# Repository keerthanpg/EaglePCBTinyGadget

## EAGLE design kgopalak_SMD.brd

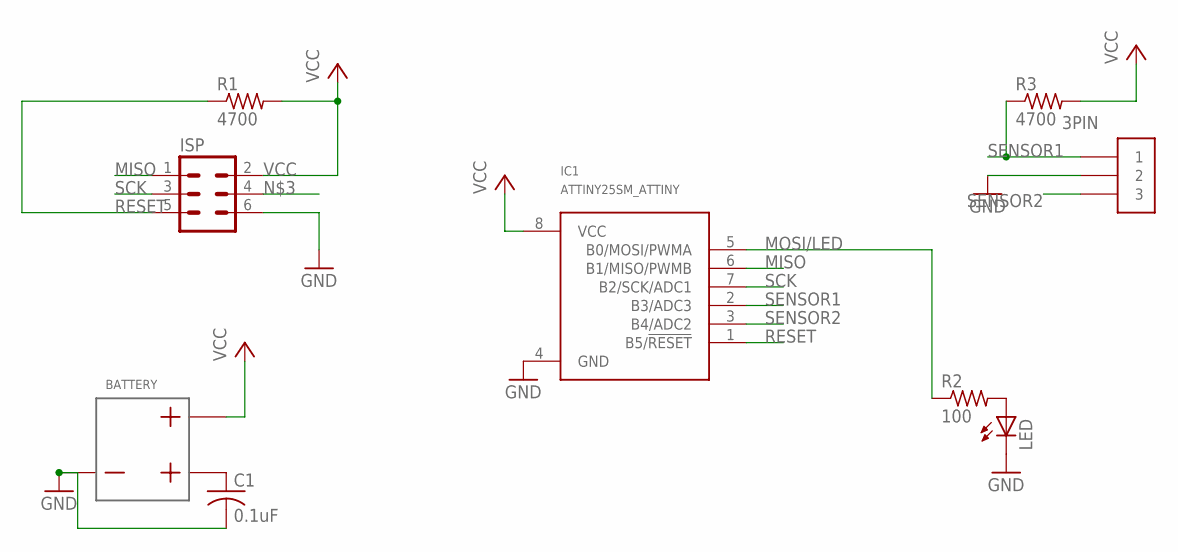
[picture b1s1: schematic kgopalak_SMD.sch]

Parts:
3PIN: 3PINCONSM_3PIN; SM3PIN
BATTERY: BATTERYSM_BA2032; BA2032SM
C1: 0.1uF; C0402
IC1: ATTINY25SM_ATTINY; 8S1
ISP: 6PINCON_ISPSM_6PIN; SM6PIN
LED: LEDSMLED; CHIPLED_0603
R1, R3: 4700; R0402
R2: 100; R0402

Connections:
GND: 3PIN.2, BATTERY.1, C1.2, IC1.4 (GND), ISP.6, LED.C
MISO: IC1.6 (B1/MISO/PWMB), ISP.1
MOSI/LED: IC1.5 (B0/MOSI/PWMA), R2.1
unnamed: LED.A, R2.2
unnamed: BATTERY.3, C1.1
RESET: IC1.1 (B5/!RESET), ISP.5, R1.1
SCK: IC1.7 (B2/SCK/ADC1), ISP.3
SENSOR1: 3PIN.1, IC1.2 (B3/ADC3), R3.1
SENSOR2: 3PIN.3, IC1.3 (B4/ADC2)
VCC: BATTERY.2, IC1.8 (VCC), ISP.2, R1.2, R3.2

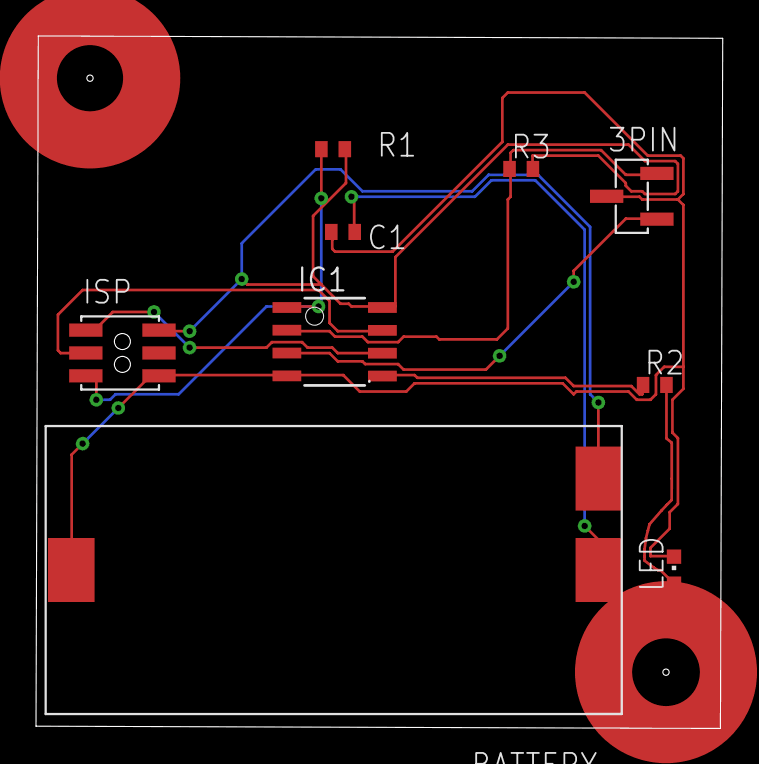
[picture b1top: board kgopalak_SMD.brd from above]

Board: 2 copper layers, 38.2 x 38.5 mm, 9 parts (0 on the bottom side), 10 nets.
